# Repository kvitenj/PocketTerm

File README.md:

# PocketTerminal

A credit card-sized computer for wireless and wired communication debugging

---

## 🔖 Overview

The project is inspired by the [M5Stack Cardputer](https://docs.m5stack.com/en/core/Cardputer%20V1.1).

The key features:

- Credit card size to easily fit in any pocket
- QWERTY tactile keyboard for easy and fast command and data input
- "Large" 2.2-inch OLED monochrome LCD with 128x32 resolution. It is monochrome and has less resolution than M5Stack, but it is larger and fits nicely for text terminal data
- ESP32 module as a central processing unit capable of Bluetooth and WiFi communication
- SD card slot for Data storage
- Large and slim battery for long-term operation
- UART, SPI, I2C(TBD) I/O for wired communication debugging
- CC1101 and LoRa(TBD) transceivers for wireless communication debugging

---

## 📁 Repository Contents

| File | Description |
|------|-------------|
| `PocketTerminalHW` | Folder containing the KiCAD project, PCB and Schematic |
| `images` | Folder containing the concept renders | 
| `LICENSE` | This repository license file |
| `README.md` | This file |

---

## 📬 Contributing

You may submit pull requests or fork the repo. But since it is a hobby project, I may respond with significant delays

---

## 🌸 License

Licensed under the [Flower License](./LICENSE) 🌸

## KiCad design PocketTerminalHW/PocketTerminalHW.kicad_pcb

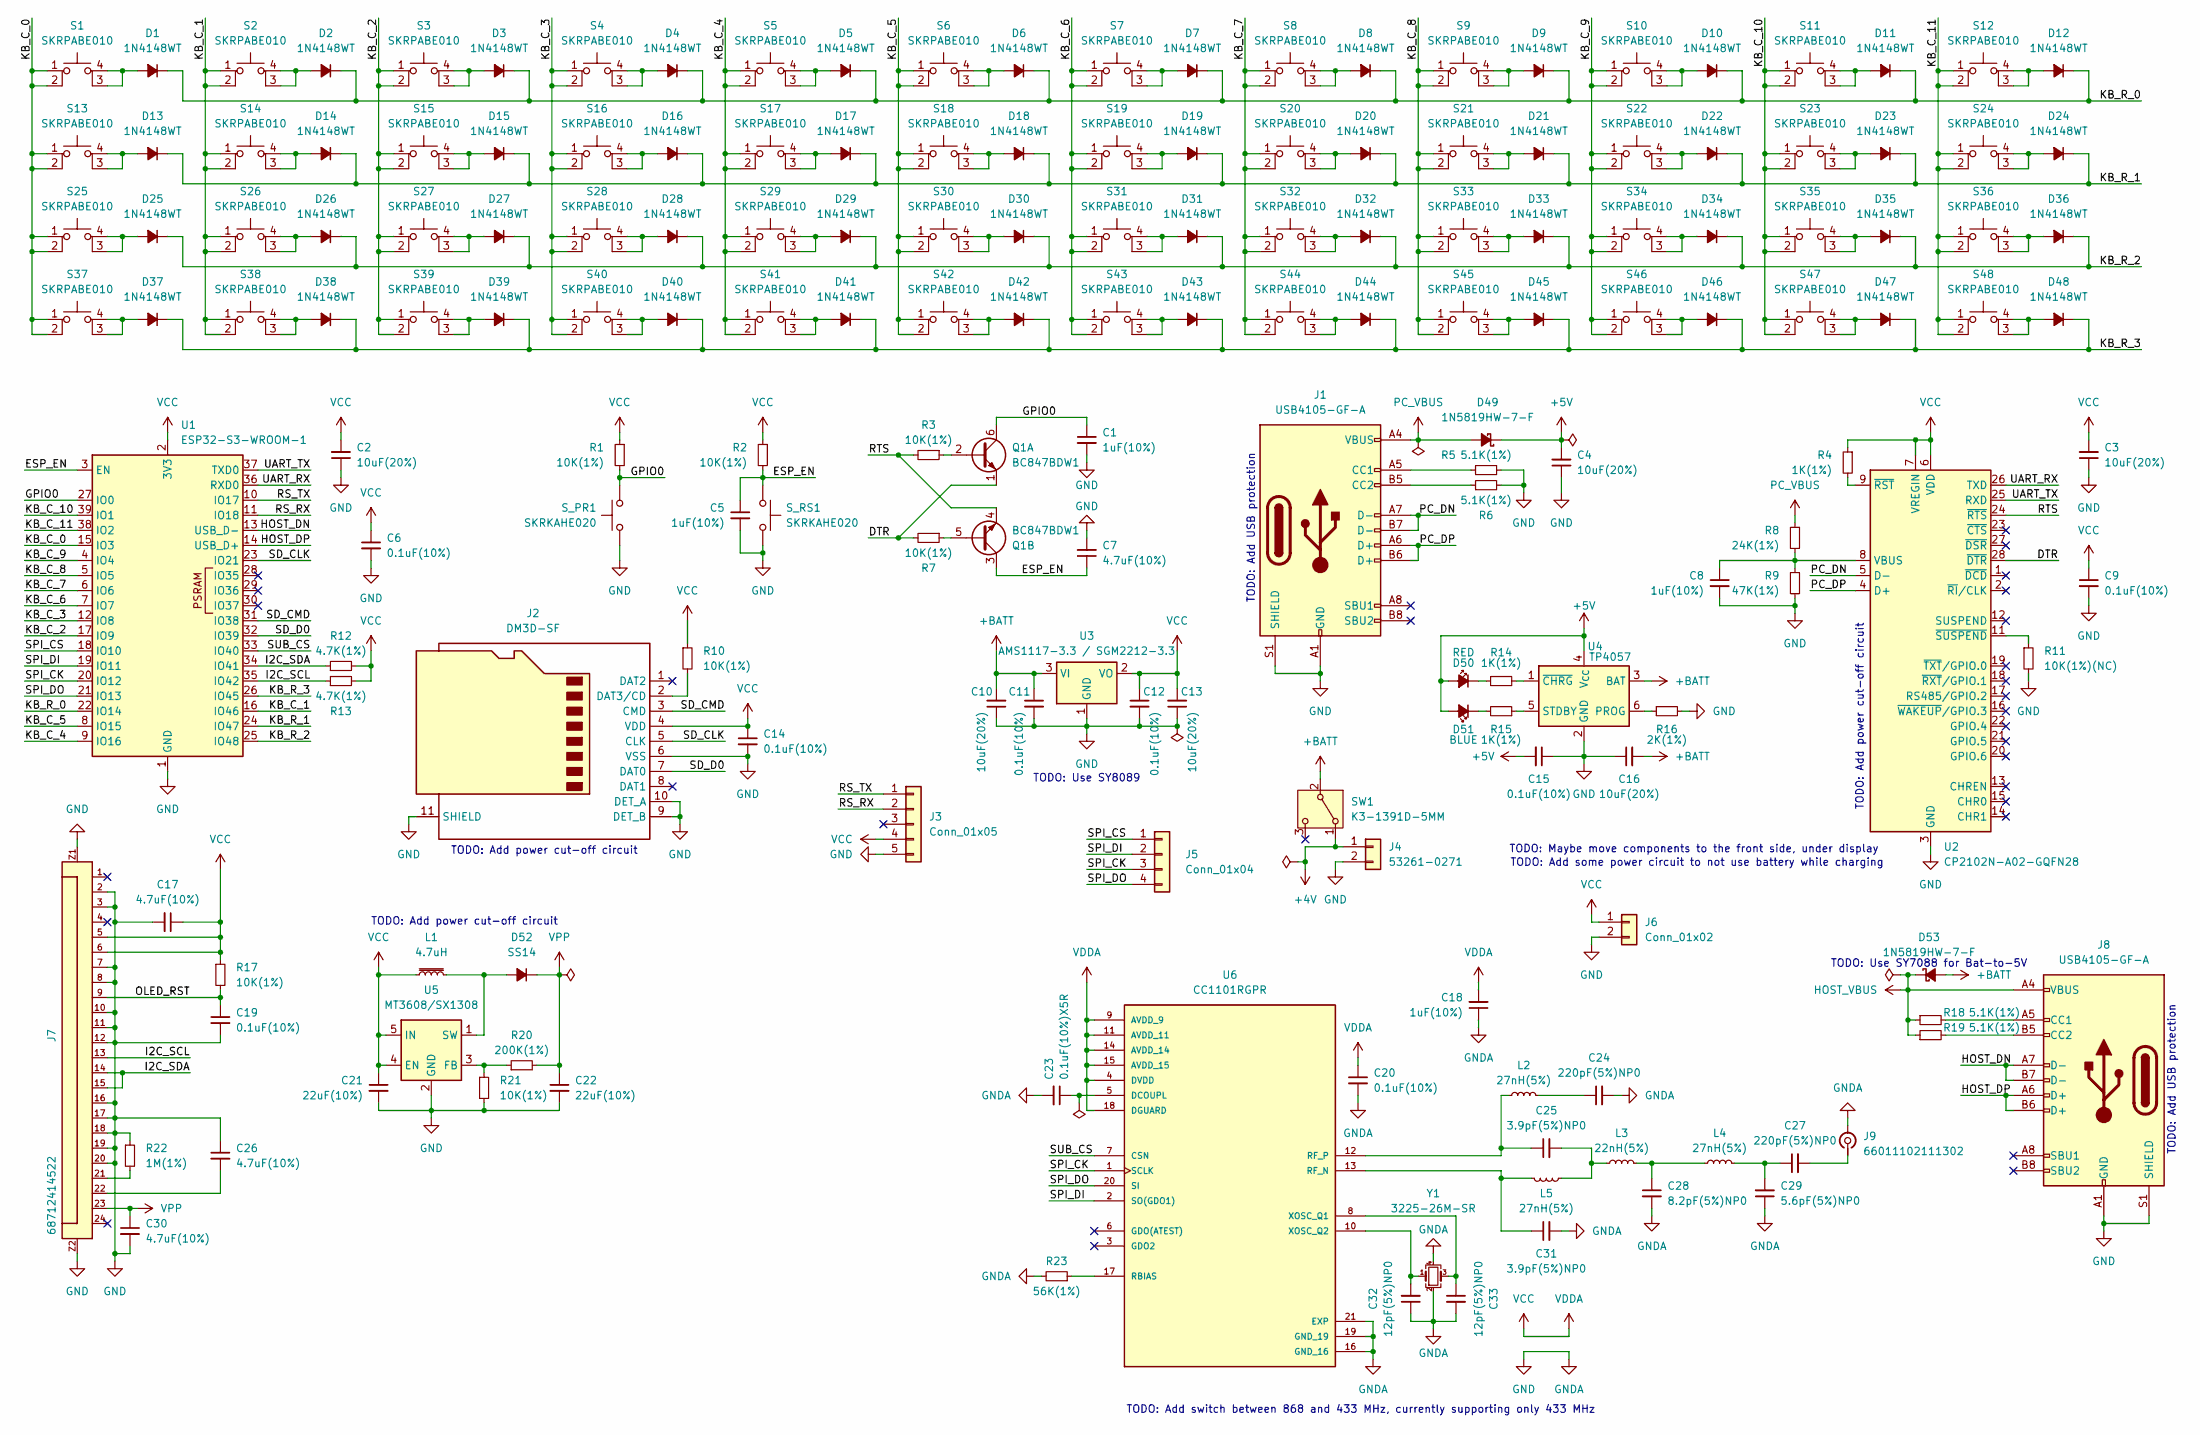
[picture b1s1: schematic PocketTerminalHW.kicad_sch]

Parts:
C1, C5, C8, C18: 1uF(10%); C_0402_1005Metric_Pad0.74x0.62mm_HandSolder
C2, C3, C4, C10, C13, C16: 10uF(20%); C_0402_1005Metric_Pad0.74x0.62mm_HandSolder
C6, C9, C11, C12, C14, C15, C19, C20: 0.1uF(10%); C_0402_1005Metric_Pad0.74x0.62mm_HandSolder
C7, C17, C26, C30: 4.7uF(10%); C_0402_1005Metric_Pad0.74x0.62mm_HandSolder
C21, C22: 22uF(10%); C_0603_1608Metric_Pad1.08x0.95mm_HandSolder
C23: 0.1uF(10%)X5R; C_0402_1005Metric_Pad0.74x0.62mm_HandSolder
C24, C27: 220pF(5%)NP0; C_0402_1005Metric_Pad0.74x0.62mm_HandSolder
C25, C31: 3.9pF(5%)NP0; C_0402_1005Metric_Pad0.74x0.62mm_HandSolder
C28: 8.2pF(5%)NP0; C_0402_1005Metric_Pad0.74x0.62mm_HandSolder
C29: 5.6pF(5%)NP0; C_0402_1005Metric_Pad0.74x0.62mm_HandSolder
C32, C33: 12pF(5%)NP0; C_0402_1005Metric_Pad0.74x0.62mm_HandSolder
D1, D2, D3, D4, D5, D6, D7, D8, D9, D10, D11, D12, D13, D14, D15, D16, D17, D18, D19, D20, D21, D22, D23, D24, D25, D26, D27, D28, D29, D30, D31, D32, D33, D34, D35, D36, D37, D38, D39, D40, D41, D42, D43, D44, D45, D46, D47, D48: 1N4148WT; D_SOD-523
D49, D53: 1N5819HW-7-F; D_SOD-123
D50: RED; LED_0402_1005Metric
D51: BLUE; LED_0402_1005Metric
D52: SS14; D_SMA
J1, J8: USB4105-GF-A; USB_C_Receptacle_GCT_USB4105-xx-A_16P_TopMnt_Horizontal
J2: DM3D-SF; microSD_HC_Hirose_DM3D-SF
J3: Conn_01x05; PinSocket_1x05_P2.54mm_Vertical
J4: 53261-0271; SolderWire-0.1sqmm_1x02_P3.6mm_D0.4mm_OD1mm
J5: Conn_01x04; PinHeader_1x04_P2.54mm_Horizontal
J6: Conn_01x02; PinHeader_1x02_P2.54mm_Horizontal
J7: 68712414522
J9: 66011102111302; WR-MMCX_Wuerth_66011102111302_Horizontal
L1: 4.7uH; L_Coilcraft_LPS4018
L2, L4, L5: 27nH(5%); L_0402_1005Metric_Pad0.77x0.64mm_HandSolder
L3: 22nH(5%); L_0402_1005Metric_Pad0.77x0.64mm_HandSolder
Q1: BC847BDW1; SOT-363_SC-70-6_Handsoldering
R1, R2, R3, R7, R10, R17, R21: 10K(1%); R_0402_1005Metric_Pad0.72x0.64mm_HandSolder
R4, R14, R15: 1K(1%); R_0402_1005Metric_Pad0.72x0.64mm_HandSolder
R5, R6, R18, R19: 5.1K(1%); R_0402_1005Metric_Pad0.72x0.64mm_HandSolder
R8: 24K(1%); R_0402_1005Metric_Pad0.72x0.64mm_HandSolder
R9: 47K(1%); R_0402_1005Metric_Pad0.72x0.64mm_HandSolder
R11: 10K(1%)(NC); R_0402_1005Metric_Pad0.72x0.64mm_HandSolder
R12, R13: 4.7K(1%); R_0402_1005Metric_Pad0.72x0.64mm_HandSolder
R16: 2K(1%); R_0402_1005Metric_Pad0.72x0.64mm_HandSolder
R20: 200K(1%); R_0402_1005Metric_Pad0.72x0.64mm_HandSolder
R22: 1M(1%); R_0402_1005Metric_Pad0.72x0.64mm_HandSolder
R23: 56K(1%); R_0402_1005Metric_Pad0.72x0.64mm_HandSolder
S1, S2, S3, S4, S5, S6, S7, S8, S9, S10, S11, S12, S13, S14, S15, S16, S17, S18, S19, S20, S21, S22, S23, S24, S25, S26, S27, S28, S29, S30, S31, S32, S33, S34, S35, S36, S37, S38, S39, S40, S41, S42, S43, S44, S45, S46, S47, S48: SKRPABE010; SW4_SKRPABE010_ALPS
SW1: K3-1391D-5MM; SW_SPDT_PCM12
S_PR1: SKRKAHE020; SW_Push_SPST_NO_Alps_SKRK
S_RS1: SKRKAHE020; SW_Push_SPST_NO_Alps_SKRK
U1: ESP32-S3-WROOM-1
U2: CP2102N-A02-GQFN28; QFN-28-1EP_5x5mm_P0.5mm_EP3.35x3.35mm
U3: AMS1117-3.3 / SGM2212-3.3; SOT-223-3_TabPin2
U4: TP4057; TSOT-23-6
U5: MT3608/SX1308; SOT-23-6_Handsoldering
U6: CC1101RGPR; QFN-20-1EP_4x4mm_P0.5mm_EP2.5x2.5mm; PARTREV 6-May-2020
Y1: 3225-26M-SR; Crystal_SMD_3225-4Pin_3.2x2.5mm

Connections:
+4V: J4.1, SW1.1 (A)
+5V: C4.2, C15.2, D49.1 (K), D50.2 (A), D51.2 (A), U4.4 (V_{CC})
+BATT: C10.2, C11.1, C16.2, D53.2 (A), SW1.2 (B), U3.3 (VI), U4.3 (BAT)
/DTR: Q1.1 (E1), R7.2, U2.28 (~DTR)
/ESP_EN: C5.1, C7.1, Q1.3 (C2), R2.2, S_RS1.1, U1.3 (EN)
/GPIO0: C1.1, Q1.6 (C1), R1.2, S_PR1.1, U1.27 (IO0)
/HOST_DN: J8.A7 (D-), J8.B7 (D-), U1.13 (USB_D-)
/HOST_DP: J8.A6 (D+), J8.B6 (D+), U1.14 (USB_D+)
/I2C_SCL: J7.13, R13.1, U1.35 (IO42)
/I2C_SDA: J7.14, J7.15, R12.1, U1.34 (IO41)
/KB_C_0: S1.1, S1.2, S13.1, S13.2, S25.1, S25.2, S37.1, S37.2, U1.15 (IO3)
/KB_C_1: S2.1, S2.2, S14.1, S14.2, S26.1, S26.2, S38.1, S38.2, U1.16 (IO46)
/KB_C_2: S3.1, S3.2, S15.1, S15.2, S27.1, S27.2, S39.1, S39.2, U1.17 (IO9)
/KB_C_3: S4.1, S4.2, S16.1, S16.2, S28.1, S28.2, S40.1, S40.2, U1.12 (IO8)
/KB_C_4: S5.1, S5.2, S17.1, S17.2, S29.1, S29.2, S41.1, S41.2, U1.9 (IO16)
/KB_C_5: S6.1, S6.2, S18.1, S18.2, S30.1, S30.2, S42.1, S42.2, U1.8 (IO15)
/KB_C_6: S7.1, S7.2, S19.1, S19.2, S31.1, S31.2, S43.1, S43.2, U1.7 (IO7)
/KB_C_7: S8.1, S8.2, S20.1, S20.2, S32.1, S32.2, S44.1, S44.2, U1.6 (IO6)
/KB_C_8: S9.1, S9.2, S21.1, S21.2, S33.1, S33.2, S45.1, S45.2, U1.5 (IO5)
/KB_C_9: S10.1, S10.2, S22.1, S22.2, S34.1, S34.2, S46.1, S46.2, U1.4 (IO4)
/KB_C_10: S11.1, S11.2, S23.1, S23.2, S35.1, S35.2, S47.1, S47.2, U1.39 (IO1)
/KB_C_11: S12.1, S12.2, S24.1, S24.2, S36.1, S36.2, S48.1, S48.2, U1.38 (IO2)
/KB_R_0: D1.1 (K), D2.1 (K), D3.1 (K), D4.1 (K), D5.1 (K), D6.1 (K), D7.1 (K), D8.1 (K), D9.1 (K), D10.1 (K), D11.1 (K), D12.1 (K), U1.22 (IO14)
/KB_R_1: D13.1 (K), D14.1 (K), D15.1 (K), D16.1 (K), D17.1 (K), D18.1 (K), D19.1 (K), D20.1 (K), D21.1 (K), D22.1 (K), D23.1 (K), D24.1 (K), U1.24 (IO47)
/KB_R_2: D25.1 (K), D26.1 (K), D27.1 (K), D28.1 (K), D29.1 (K), D30.1 (K), D31.1 (K), D32.1 (K), D33.1 (K), D34.1 (K), D35.1 (K), D36.1 (K), U1.25 (IO48)
/KB_R_3: D37.1 (K), D38.1 (K), D39.1 (K), D40.1 (K), D41.1 (K), D42.1 (K), D43.1 (K), D44.1 (K), D45.1 (K), D46.1 (K), D47.1 (K), D48.1 (K), U1.26 (IO45)
/OLED_RST: C19.1, J7.9, R17.2
/PC_DN: J1.A7 (D-), J1.B7 (D-), U2.5 (D-)
/PC_DP: J1.A6 (D+), J1.B6 (D+), U2.4 (D+)
/RS_RX: J3.2, U1.11 (IO18)
/RS_TX: J3.1, U1.10 (IO17)
/RTS: Q1.4 (E2), R3.2, U2.24 (~RTS)
/SD_CLK: J2.5 (CLK), U1.23 (IO21)
/SD_CMD: J2.3 (CMD), U1.31 (IO38)
/SD_D0: J2.7 (DAT0), U1.32 (IO39)
/SPI_CK: J5.3, U1.20 (IO12), U6.1 (SCLK)
/SPI_CS: J5.1, U1.18 (IO10)
/SPI_DI: J5.2, U1.19 (IO11), U6.2 (SO(GDO1))
/SPI_DO: J5.4, U1.21 (IO13), U6.20 (SI)
/SUB_CS: U1.33 (IO40), U6.7 (CSN)
/UART_RX: U1.36 (RXD0), U2.26 (TXD)
/UART_TX: U1.37 (TXD0), U2.25 (RXD)
GND: C1.2, C2.1, C3.1, C4.1, C5.2, C6.2, C7.2, C8.2, C9.2, C10.1, C11.2, C12.2, C13.1, C14.2, C15.1, C16.1, C17.2, C18.1, C19.2, C20.2, C21.2, C22.2, C23.2, C24.2, C26.1, C28.2, C29.1, C30.2, C31.2, C32.1, C33.2, J1.A1 (GND), J1.A12 (GND), J1.B1 (GND), J1.B12 (GND), J1.S1 (SHIELD), J2.6 (VSS), J2.9 (DET_B), J2.10 (DET_A), J2.11 (SHIELD), J3.5, J4.2, J6.2, J7.2, J7.3, J7.7, J7.8, J7.10, J7.11, J7.12, J7.16, J7.17, J7.18, J7.19, J7.20, J7.Z1, J7.Z2, J8.A1 (GND), J8.A12 (GND), J8.B1 (GND), J8.B12 (GND), J8.S1 (SHIELD), J9.2 (Ext), R5.2, R6.2, R9.2, R11.2, R16.2, R21.2, R22.1, R23.2, S_PR1.2, S_RS1.2, U1.1 (GND), U1.40 (GND), U1.41 (GND), U2.3 (GND), U2.29 (GND), U3.1 (GND), U4.2 (GND), U5.2 (GND), U6.16 (GND_16), U6.19 (GND_19), U6.21 (EXP), Y1.2, Y1.4
HOST_VBUS: D53.1 (K), J8.A4 (VBUS), J8.A9 (VBUS), J8.B4 (VBUS), J8.B9 (VBUS), R18.1, R19.1
unnamed: C24.1, L2.2
unnamed: C25.2, L3.1, L5.1
unnamed: C26.2, J7.22
unnamed: C27.1, C29.2, L4.2
unnamed: C28.1, L3.2, L4.1
unnamed: D1.2 (A), S1.3 (K), S1.4 (A)
unnamed: D2.2 (A), S2.3 (K), S2.4 (A)
unnamed: D3.2 (A), S3.3 (K), S3.4 (A)
unnamed: D4.2 (A), S4.3 (K), S4.4 (A)
unnamed: D5.2 (A), S5.3 (K), S5.4 (A)
unnamed: D6.2 (A), S6.3 (K), S6.4 (A)
unnamed: D7.2 (A), S7.3 (K), S7.4 (A)
unnamed: D8.2 (A), S8.3 (K), S8.4 (A)
unnamed: D9.2 (A), S9.3 (K), S9.4 (A)
unnamed: D10.2 (A), S10.3 (K), S10.4 (A)
unnamed: D11.2 (A), S11.3 (K), S11.4 (A)
unnamed: D12.2 (A), S12.3 (K), S12.4 (A)
unnamed: D13.2 (A), S13.3 (K), S13.4 (A)
unnamed: D14.2 (A), S14.3 (K), S14.4 (A)
unnamed: D15.2 (A), S15.3 (K), S15.4 (A)
unnamed: D16.2 (A), S16.3 (K), S16.4 (A)
unnamed: D17.2 (A), S17.3 (K), S17.4 (A)
unnamed: D18.2 (A), S18.3 (K), S18.4 (A)
unnamed: D19.2 (A), S19.3 (K), S19.4 (A)
unnamed: D20.2 (A), S20.3 (K), S20.4 (A)
unnamed: D21.2 (A), S21.3 (K), S21.4 (A)
unnamed: D22.2 (A), S22.3 (K), S22.4 (A)
unnamed: D23.2 (A), S23.3 (K), S23.4 (A)
unnamed: D24.2 (A), S24.3 (K), S24.4 (A)
unnamed: D25.2 (A), S25.3 (K), S25.4 (A)
unnamed: D26.2 (A), S26.3 (K), S26.4 (A)
unnamed: D27.2 (A), S27.3 (K), S27.4 (A)
unnamed: D28.2 (A), S28.3 (K), S28.4 (A)
unnamed: D29.2 (A), S29.3 (K), S29.4 (A)
unnamed: D30.2 (A), S30.3 (K), S30.4 (A)
unnamed: D31.2 (A), S31.3 (K), S31.4 (A)
unnamed: D32.2 (A), S32.3 (K), S32.4 (A)
unnamed: D33.2 (A), S33.3 (K), S33.4 (A)
unnamed: D34.2 (A), S34.3 (K), S34.4 (A)
unnamed: D35.2 (A), S35.3 (K), S35.4 (A)
unnamed: D36.2 (A), S36.3 (K), S36.4 (A)
unnamed: D37.2 (A), S37.3 (K), S37.4 (A)
unnamed: D38.2 (A), S38.3 (K), S38.4 (A)
unnamed: D39.2 (A), S39.3 (K), S39.4 (A)
unnamed: D40.2 (A), S40.3 (K), S40.4 (A)
unnamed: D41.2 (A), S41.3 (K), S41.4 (A)
unnamed: D42.2 (A), S42.3 (K), S42.4 (A)
unnamed: D43.2 (A), S43.3 (K), S43.4 (A)
unnamed: D44.2 (A), S44.3 (K), S44.4 (A)
unnamed: D45.2 (A), S45.3 (K), S45.4 (A)
unnamed: D46.2 (A), S46.3 (K), S46.4 (A)
unnamed: D47.2 (A), S47.3 (K), S47.4 (A)
unnamed: D48.2 (A), S48.3 (K), S48.4 (A)
unnamed: D50.1 (K), R14.1
unnamed: D51.1 (K), R15.2
unnamed: D52.2 (A), L1.2, U5.1 (SW)
unnamed: J1.A5 (CC1), R5.1
unnamed: J1.B5 (CC2), R6.1
unnamed: J2.2 (DAT3/CD), R10.2
unnamed: J7.21, R22.2
unnamed: J8.A5 (CC1), R18.2
unnamed: J8.B5 (CC2), R19.2
unnamed: C27.2, J9.1 (In)
unnamed: Q1.2 (B1), R3.1
unnamed: Q1.5 (B2), R7.1
unnamed: C8.1, R8.2, R9.1, U2.8 (VBUS)
unnamed: R4.2, U2.9 (~RST)
unnamed: R11.1, U2.11 (~SUSPEND)
unnamed: R16.1, U4.6 (PROG)
unnamed: R15.1, U4.5 (STDBY)
unnamed: R14.2, U4.1 (~CHRG)
unnamed: R20.1, R21.1, U5.3 (FB)
unnamed: C23.1, U6.5 (DCOUPL)
unnamed: R23.1, U6.17 (RBIAS)
unnamed: C31.1, L5.2, U6.13 (RF_N)
unnamed: C25.1, L2.1, U6.12 (RF_P)
unnamed: C33.1, U6.8 (XOSC_Q1), Y1.3
unnamed: C32.2, U6.10 (XOSC_Q2), Y1.1
PC_VBUS: D49.2 (A), J1.A4 (VBUS), J1.A9 (VBUS), J1.B4 (VBUS), J1.B9 (VBUS), R8.1
VCC: C2.2, C3.2, C6.1, C9.1, C12.1, C13.2, C14.1, C17.1, C18.2, C20.1, C21.1, J2.4 (VDD), J3.4, J6.1, J7.5, J7.6, L1.1, R1.1, R2.1, R4.1, R10.1, R12.2, R13.2, R17.1, U1.2 (3V3), U2.6 (VDD), U2.7 (VREGIN), U3.2 (VO), U5.4 (EN), U5.5 (IN), U6.4 (DVDD), U6.9 (AVDD_9), U6.11 (AVDD_11), U6.14 (AVDD_14), U6.15 (AVDD_15), U6.18 (DGUARD)
VPP: C22.1, C30.1, D52.1 (K), J7.23, R20.2

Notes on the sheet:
TODO: Add power cut-off circuit
TODO: Use SY7088 for Bat-to-5V
TODO: Add switch between 868 and 433 MHz, currently supporting only 433 MHz
TODO: Use SY8089
TODO: Maybe move components to the front side, under display
TODO: Add some power circuit to not use battery while charging
TODO: Add USB protection

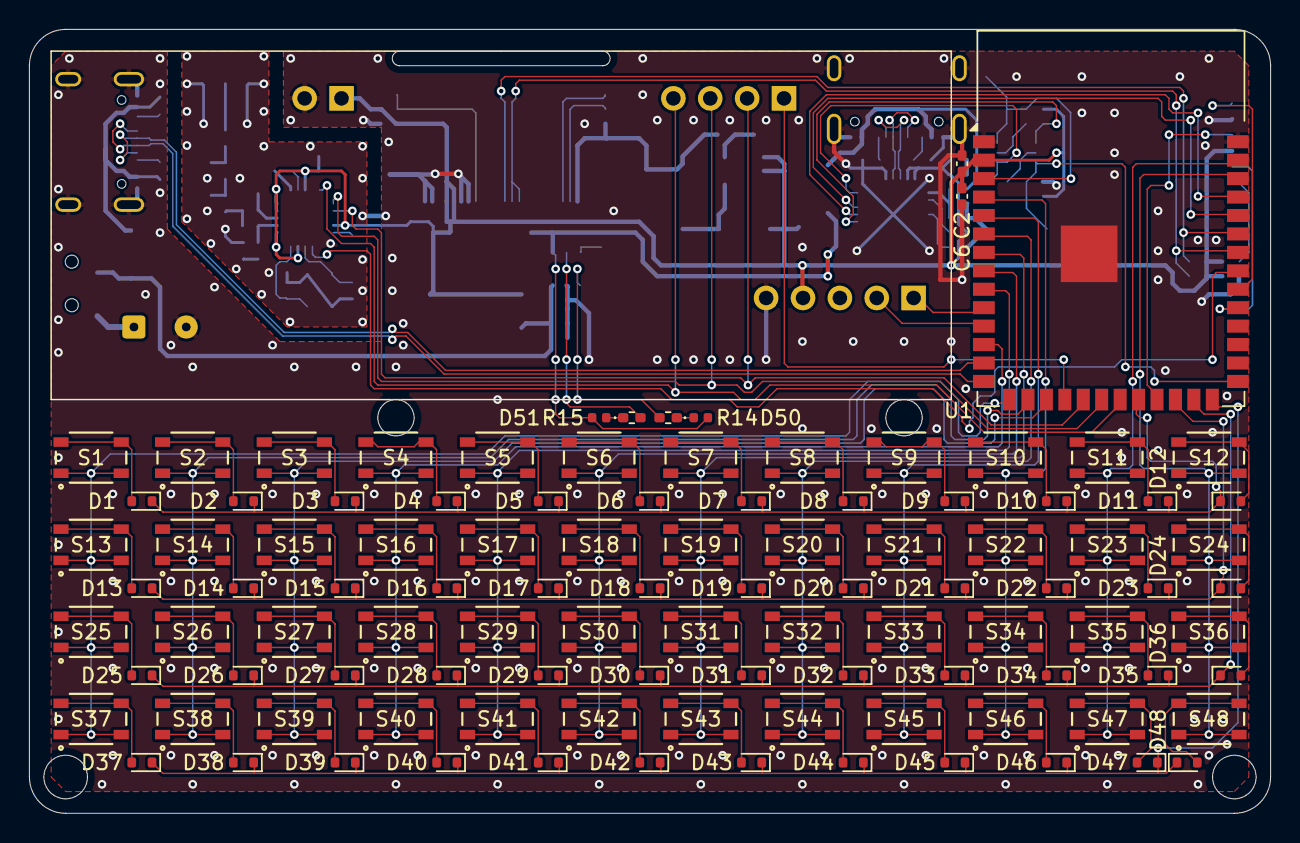
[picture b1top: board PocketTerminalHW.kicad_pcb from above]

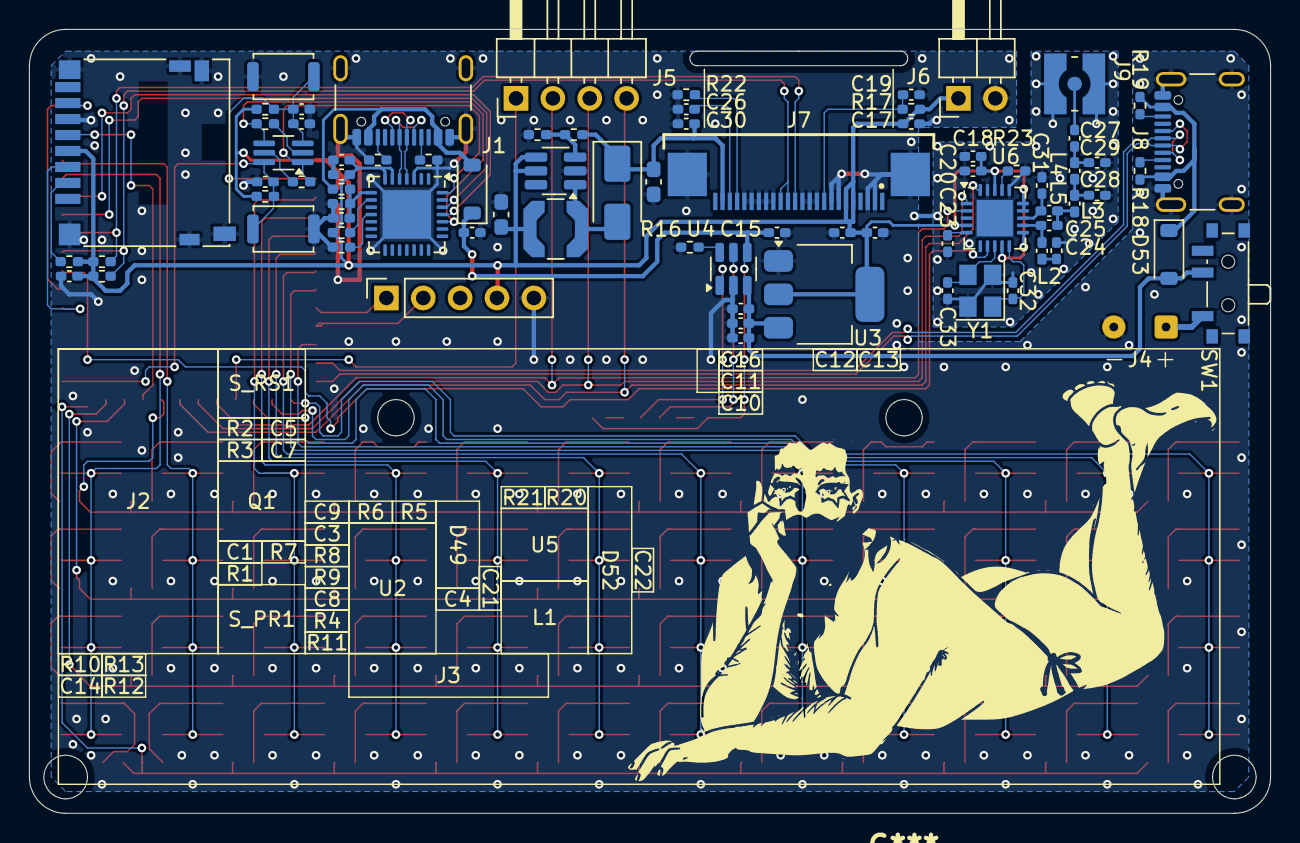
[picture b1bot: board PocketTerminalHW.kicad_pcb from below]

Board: 2 copper layers, 85.5 x 54.0 mm, 182 parts (79 on the bottom side), 125 nets.

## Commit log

2025-08-27 Schematic and PCB progress Changed ESP module to S3 Added Battery outline Added Program buttons, Auto Program schematic, USB-UART without USB-C socket, SD card socket Finished: ESP, Buttons, Programm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
2025-08-28 Remove componments folder
2025-08-28 Pin adjustments for SD Add display ribbon cable hole
2025-08-28 Added OLED schematic
2025-09-03 Schematic and board progress
    Updated gitignore and removed some ignored files
    Added power schematic with battery chagrer
    Some adjustments to components
2025-09-05 Board adjustments and some renders
2025-09-09 CC1101 progress
2025-09-09 Added USB host and finished CC1110 schematic
2025-09-09 ERC correction
2025-09-11 Minor schematic changes and some PCB tracing progress
2025-09-12 PCB progress
2025-09-14 Finalized firt prototype Completed PCB design Finalized schematic
2025-09-14 Minor silkscreen update
2025-09-16 Minor adjustments
2025-09-18 Minor PCB changes
2025-09-18 Project rename and minor PCB changes
2025-09-18 Project rename
2025-09-19 Switch images to PCB renders
2025-09-20 Minor PCB adjustments, change charger to TP4057
2025-09-20 Moved mounting holes
2025-09-22 Minor cnages to cap values
2025-09-25 Minor changes
2025-12-05 Added photos of prototype
2026-03-02 Second proto WIP
2026-03-02 Corrected file attributes
